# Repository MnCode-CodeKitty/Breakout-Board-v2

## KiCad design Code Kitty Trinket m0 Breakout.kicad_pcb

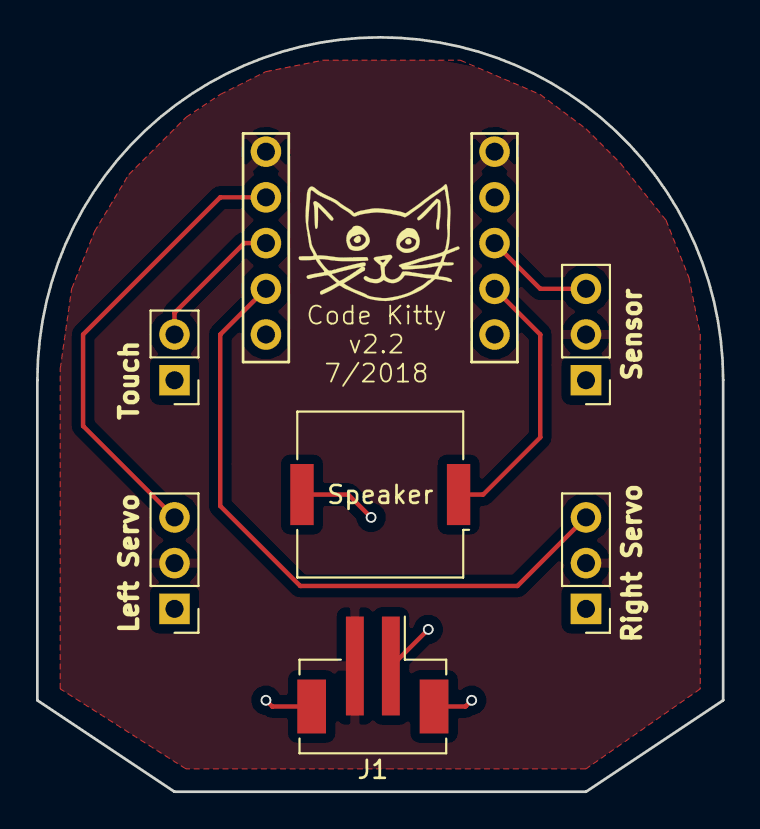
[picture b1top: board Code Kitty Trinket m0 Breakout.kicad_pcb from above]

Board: 2 copper layers, 38.1 x 41.9 mm, 7 parts (0 on the bottom side), 7 nets.

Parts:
J1: Power; JST_PH_B2B-PH-SM4-TB_02x2.00mm_Straight
P1: Left Servo; Pin_Header_Straight_1x03_Pitch2.54mm
P2: Right Servo; Pin_Header_Straight_1x03_Pitch2.54mm
P3: Sensor; Pin_Header_Straight_1x03_Pitch2.54mm
P4: Touch; Pin_Header_Straight_1x02_Pitch2.54mm
Speaker: PIEZO; Buzzer_Murata_PKMCS0909E4000-R1
m1: Trinket-m0

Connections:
BUZZ: Speaker.1, m1.4
GND: J1.1, P1.1, P2.1, P3.1, P4.1, Speaker.2, m1.2
LSERVO: P1.3, m1.7
RSERVO: P2.3, m1.9
SENS: P3.3, m1.3
Touch: P4.2, m1.8
VCC: J1.2, P1.2, P2.2, P3.2, m1.1, m1.6

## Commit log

2018-06-11 New board design!
2018-06-11 Fixed board traces in filled areas
2018-07-11 Version 2.1 redesign
2018-07-11 added ground vias for JST connector and Speaker
2018-07-12 Fixed text on board to say Code Kitty 2.2
